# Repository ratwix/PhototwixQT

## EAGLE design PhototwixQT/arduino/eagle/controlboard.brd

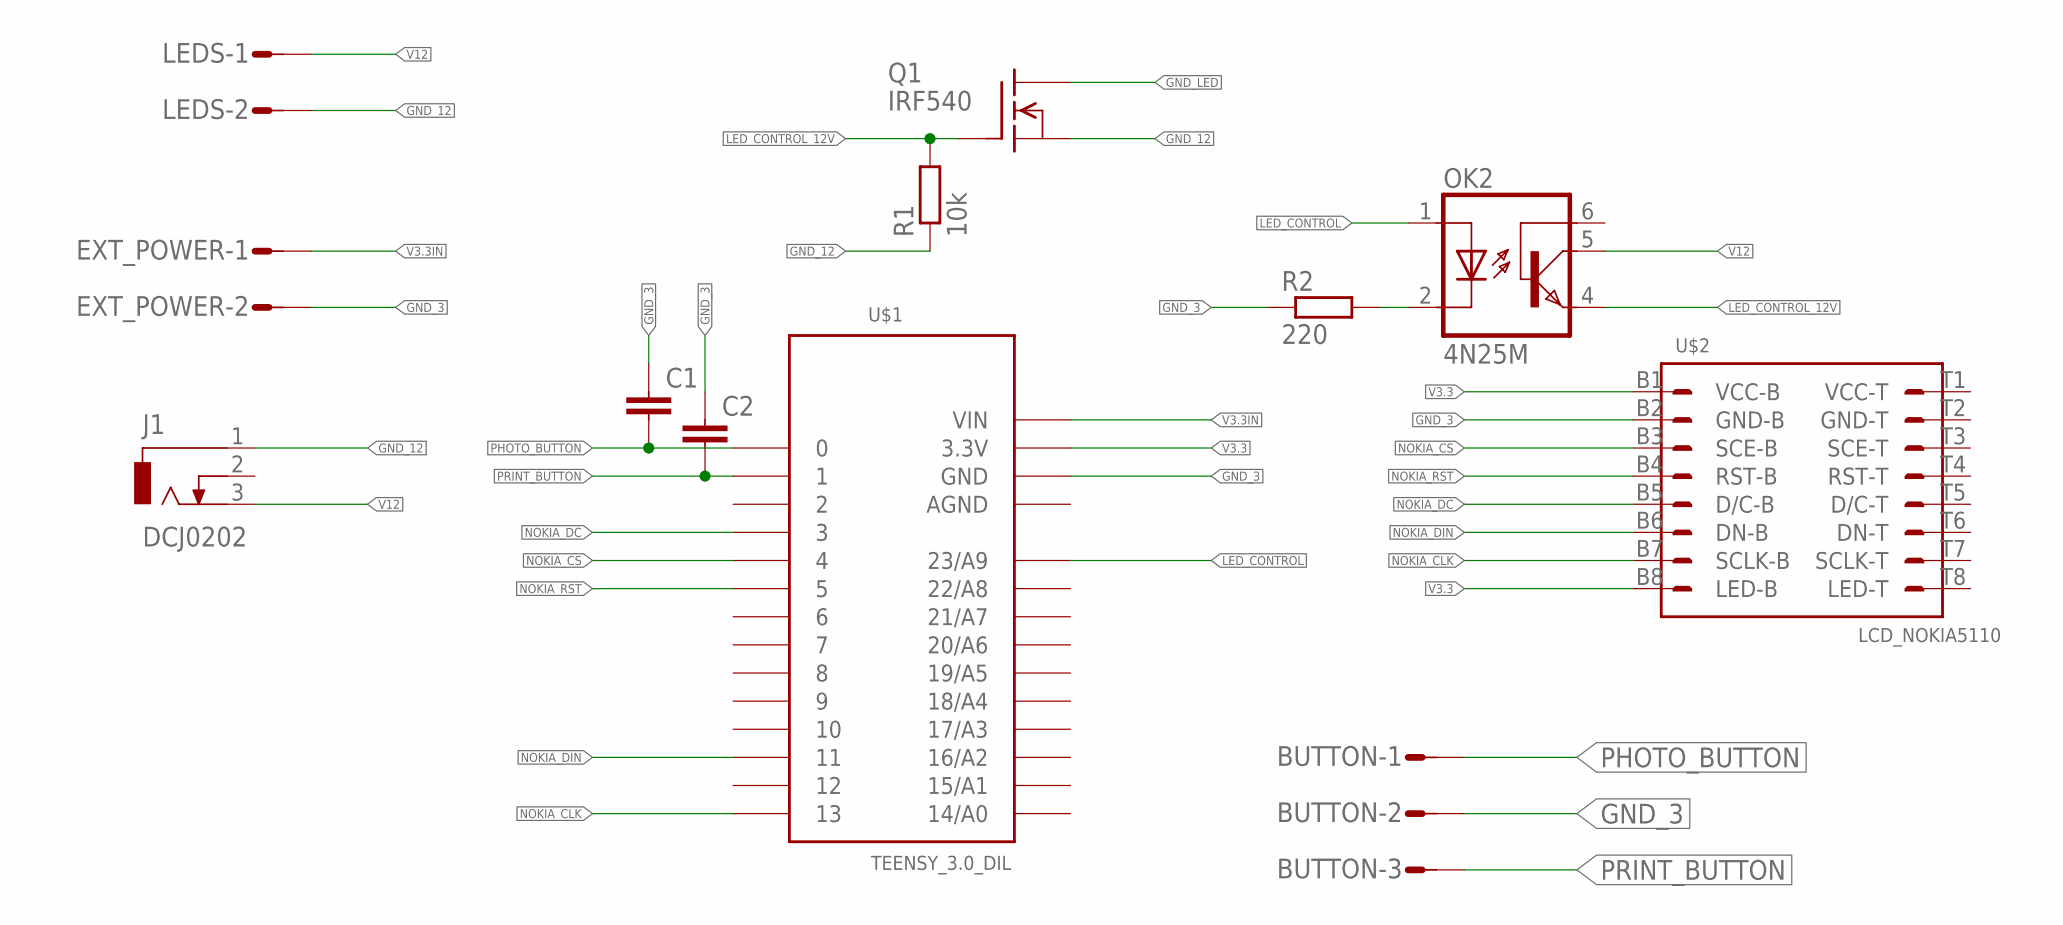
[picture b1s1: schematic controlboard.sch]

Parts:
BUTTON: L03P
C1, C2: C-EU025-025X050; C025-025X050
EXT_POWER: S02P
J1: DCJ0202
LEDS: L02P
OK2: 4N25M; DIL06
Q1: IRF540; TO220
R1: 10k; 0207/10
R2: 220; 0207/10
U$1: TEENSY_3.0_DIL; TEENSY3-DIL
U$2: LCD_NOKIA5110; NOKIA5110

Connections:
AGND: U$1.AGND
GND_3: BUTTON.2, C1.1, C2.1, EXT_POWER.2, R2.1, U$1.GND, U$2.B2 (GND-B)
GND_12: J1.1, LEDS.2, Q1.3 (S), R1.1
GND_LED: Q1.2 (D)
LED_CONTROL: OK2.1 (A), U$1.23/A9
LED_CONTROL_12V: OK2.4 (EMI), Q1.1 (G), R1.2
unnamed: OK2.2 (C), R2.2
NOKIA_CLK: U$1.13, U$2.B7 (SCLK-B)
NOKIA_CS: U$1.4, U$2.B3 (SCE-B)
NOKIA_DC: U$1.3, U$2.B5 (D/C-B)
NOKIA_DIN: U$1.11, U$2.B6 (DN-B)
NOKIA_RST: U$1.5, U$2.B4 (RST-B)
PHOTO_BUTTON: BUTTON.1, C1.2, U$1.0
PRINT_BUTTON: BUTTON.3, C2.2, U$1.1
V3.3: U$1.3.3V, U$2.B1 (VCC-B), U$2.B8 (LED-B)
V3.3IN: EXT_POWER.1, U$1.VIN
V12: J1.3, LEDS.1, OK2.5 (COL)

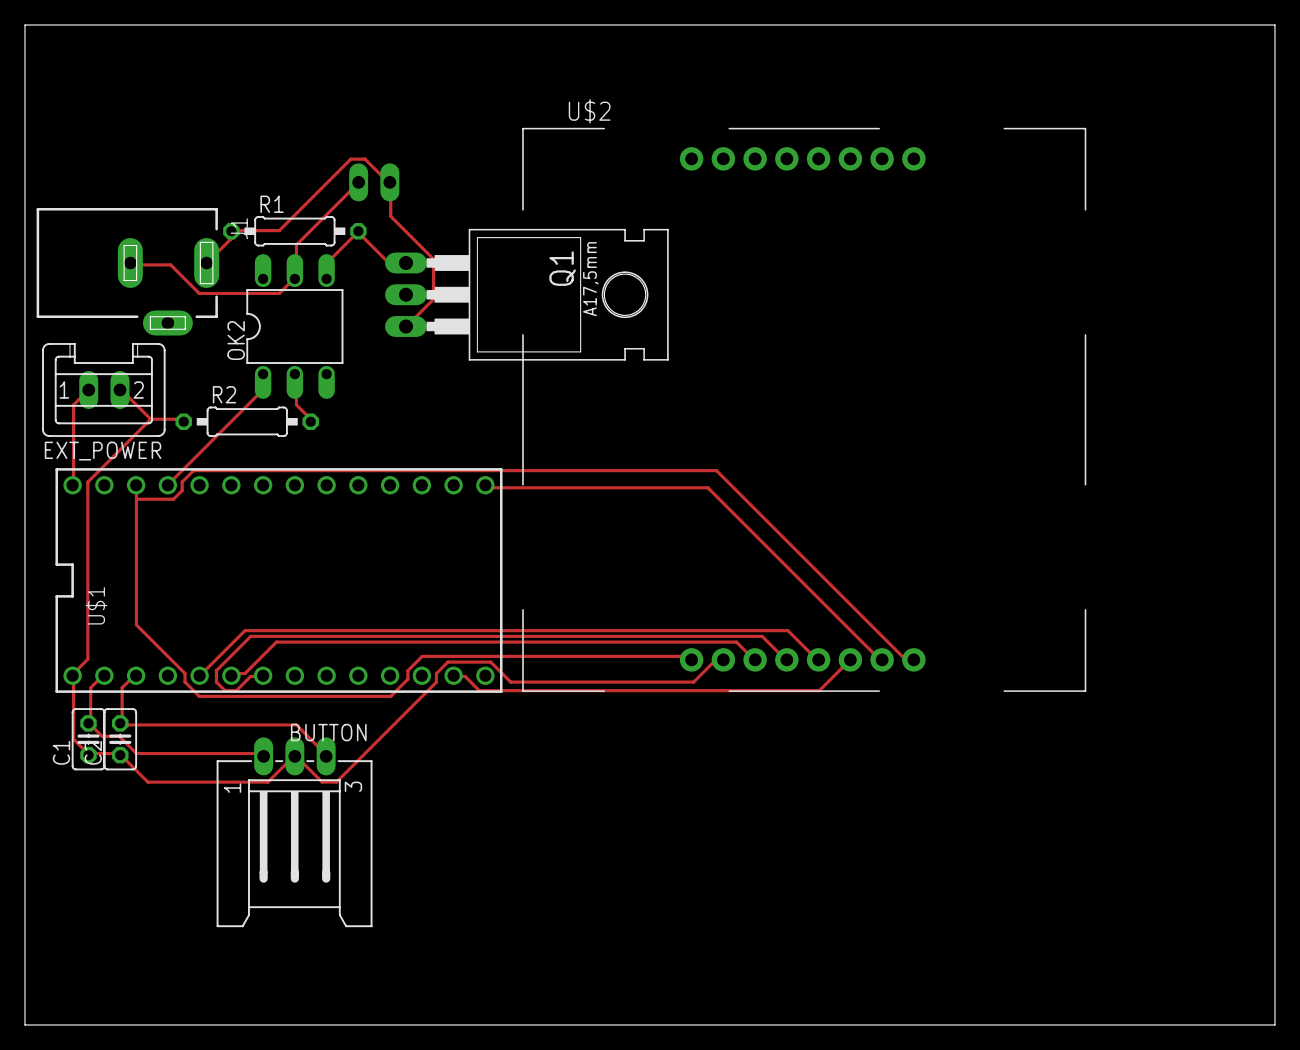
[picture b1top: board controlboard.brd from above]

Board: 2 copper layers, 100.0 x 80.0 mm, 12 parts (1 on the bottom side), 15 nets.

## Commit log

2015-06-29 Javascript stuff
2015-06-29 From javascript to C++
2015-07-01 move to C++
2015-07-05 add link for templates between C++ and QML
2015-07-08 serialise config step 1
2015-07-08 test
2015-07-08 Serialisation OK
2015-07-26 Test if file template exists before create it
2015-07-27 Add edit template screen
2015-07-28 Add photo position when config template
2015-07-29 Template photo position. Update
2015-07-29 template config update
2015-07-30 Config Template works + Serialisation
2015-07-30 First screen selection + route to photo page
2015-08-03 Add gallery creation
2015-08-03 Add image BusyIndicator
2015-08-03 State base transitions with animation
2015-08-04 Photo process in progress
2015-08-04 start photo process
2015-08-05 photoboot photos
2015-08-06 rotation and application path fixed
2015-08-06 Add effect control panel
2015-08-07 UI improvement
2015-08-07 Add effect. Bug on QT 5.5 (test works on QT 5.4)
2015-08-11 Simplify effects. Grayscale and Sepia works
2015-08-11 Add new sepia and new filter
2015-08-12 Add photo tumbnail. Next step, gallery
2015-08-12 Add TODO
2015-08-13 Gallery Stack
2015-08-17 Gallery Management
2015-08-17 Serialisation & bug correction
2015-08-18 Serialize & Unserialize Photo Gallery
2015-08-18 delete
2015-08-19 print first step
2015-08-19 Config management
2015-08-19 Config
2015-08-20 Bug correction & message display
2015-08-21 print cutter management
2015-08-21 Re-edit photos
2015-08-21 Reduire le champ de la camera : ok
2015-08-24 Arduino management
2015-08-31 Add print management
2015-09-02 Particle and sound
2015-09-03 Add new visual
2015-09-10 add keyboard
2015-09-13 Add password to access config
2015-09-15 Manage background. Center template choise
2015-09-17 Fond d'ecran et bug de date
2015-09-23 Bug de path linux
2015-09-26 Compatibilité Arduino linux. Gestion de la resolution de la camera
2015-10-06 Travail sur les effets.
2015-10-07 Ajout des effets
2015-10-09 Effect management again
2015-10-09 Add printer max counter
2015-10-18 Improvement & bug correction. Admin page with admin and normal password Standalone version.
2015-10-18 Copy to key
2015-10-27 add website
2015-10-29 Share first shot
2015-10-29 Update website
2016-01-11 Gestion photo 2
2016-01-12 Review photo process
2016-01-25 Mail first step
2016-01-26 Mail working
2016-01-28 Camera res, camera preview for focus, email saved, bug correction
2016-01-28 Eagle cardboard
2016-03-09 Bugs and template delete
2016-03-16 Bug config
2016-03-16 Remove particle : high CPU load
2016-04-17 But correction. Copy display
2016-04-22 Bug correction : last delete template
